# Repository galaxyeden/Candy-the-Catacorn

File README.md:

# Candy the Catacorn 🐱 + 🦄

[Update - I'm currently planning a board revision to make this easier to make with more obtainable parts]

Catacorn Badge :D I don't care how you spell it, I've spelled it catacorn for years. Caticorn is equally valid! It's really small, and cute - but you should be able to program it to do a lot of things.

You can [order from OSH Park](https://oshpark.com/shared_projects/pnVDiM8w) - that's not a sponsored link, and they're by no means the cheapest place to order from, I only link as they're probably the cheapest way to get a small number of purple boards with a lead-free finish (good as they'll be handled!) - and their service has always been good to me.

## Background

I have wanted to learn more about electrical engineering and the 'hardware' side of things, so have started playing with dev boards including the Adafruit Trinket M0, which is the board that inspired this project. But none of them were catacorn enough, so I decided to make one :)

It's also a great way to teach other people how to create microcontroller projects!

## Copyright/Liability

I'm not a lawyer, I believe everything I've based this on is licensed in a way I can draw inspiration, but let me know if you want me to get rid of something. All my work is Creative Commons, see license file. Also, I'm obviously not responsible for injuries or anything like that - this is definitely not a safety-tested, commercial project. Build at your own risk. It probably won't even work :)

## Basic Features

- ATSAMD21 microcontroller (ARM Cortext M0)
- Lots of LEDs, including two RGB ones (Dotstar-compatible)
- Two capacitive touch zones (ears)
- Native USB (you can even use it as a keyboard, hopefully)
- Probably a fair number of bugs and bad design decisions!

## Bill of Materials

| Component                               | Manufacturer                 | Qty |
|-----------------------------------------|------------------------------|-----|
| This board                              | Whoever you choose           | 1   |
| ATSAMD21E18A-AU-ND                      | Microchip Technology         | 1   |
| S2B-PH-SM4-TB(LF)(SN)                   | JST                          | 1   |
| 1uF 0603 Capacitor                      | Any                          | 2   |
| 10uF 0603 Capacitor                     | Any                          | 2   |
| APA102-5050 or Equivalent (e.g. SK9822) | APA Electronic Co (or other) | 2   |
| JE2835AWT-00-0000-000A0ZF940E           | Cree Inc                     | 2   |
| Pink LED 0805                           | Generic                      | 2   |
| Turquoise LED 0805                      | Generic                      | 3   |
| UV/Purple LED 0805                      | Generic                      | 3   |
| AP2112K-3.3TRG1                         | Diodes Incorporated          | 1   |
| DSS14UTR                                | SMC Diode Solutions          | 2   |
| USB3076-30-A                            | GCT                          | 1   |
| 150 Ohm 1206 Resistor                   | Any                          | 2   |
| 180 Ohm 0805 Resistor                   | Any                          | 2   |
| 180 Ohm 0603 Resistor                   | Any                          | 3   |
| 330 Ohm 0805 Resistor                   | Any                          | 3   |
| TL3342 Switch (or equivalent)           | E-Switch (or generic)        | 1   |

## How to use?

This board is intended to be used with either CircuitPython or [PlatformIO](https://platformio.org/). I have cloned and modified others [bootloader](https://github.com/MermaidAllie/uf2-samdx1/tree/master/build/alliecat_candythecatacorn) and [CircuitPython firmware](https://github.com/MermaidAllie/circuitpython/blob/5.0.x/ports/atmel-samd/build-alliecat_candythecatacorn/firmware.uf2). These are very similar to the Adafruit Trinket M0, just rebranded basically, and you can use Adafruit Trinket M0 bootloader/firmware with a lot of success (it's how I prototyped this).

I have also included PlatformIO code and board configuration.

## Thanks

Thank you to the following people:

- Ladyada and [Adafruit](https://learn.adafruit.com/how-to-program-samd-bootloaders/trinket-m0-wiring) - for building excellent products and teaching people electronics. I used a lot of Trinket M0's in prototyping this. Seriously, people, go buy their products - they're fantastic (and the boards are way cuter than some others, especially look at the Metro M4 Express - it's just adorable).

- Various inspirations for the catacorn, but especially to the kid who asked me to paint their face as a catacorn when I was face painting some years ago. It was the first time I really started thinking what the features of a catacorn should be like. I hope you're doing well today, and I wish you all the best in life :) - also to the many people who've drawn catacorns (and caticorns and unicats) online, and I've taken inspiration from.

- Also, on that note, credit to [Lisa Frank](https://lisafrank.com/) because cute Lisa Frank images were one of my childhood inspirations, and they're just awesome and made me like this style of art. A Google image search gave me more ideas for how to draw the board outline and even how to place components to be part of the art (e.g. using a capacitor as a nose, as one drawing I found had a very square nose). The purple Lisa Frank cat, especially, gave me the idea for how the whiskers could work on a component-kitty. And, only in Lisa Frank land do RGB LED cat eyes make sense :) 

- I found [this image from Freepik](https://www.freepik.com/free-vector/kawaii-style-unicorn-character-collection_4697393.htm#page=1&query=kawaii%20unicorn&position=7) which gave me inspiration for the general shape of the base (I needed something flatter than most to get the micro USB port in, and I liked how the cat's belly sat down) and head angle of the catacorn, and also for the style of the heart outline on the cheek. That said, Candy isn't a clone of anyone else's catacorn, with her tiny little horn and big glowing glittery heart, she has her own place in the world - and many others also provided inspiration. So credit to everyone who's drawn a catacorn that's in the first few pages of Google Images results :D

- [Emojipedia](https://emojipedia.org/) came in really useful to for bits of emoji-inspired inspiration, and the capacitive touch zones (which are the heart emoji from a font on my system).

- Q - for being an awesome friend who has helped with so much of the EDA side of working this all out. Thank you for answering late night messages with silly questions!

- Charlie - for coming up with the name Candy! I love you bestie :D Without your encouragement and inspiration, I wouldn't have achieved half the things I have with tech. Thank you <3

- JoJo Siwa - because the inspirational quote comes from one of your songs, and your concert on the [D.R.E.A.M. tour](https://www.jojodreamtour.com/) I went to in Cardiff was amazing. I'm not sure if it's your original quote tho, so I didn't quote it as you - I think I've heard it before? Either way, very inspiring performance! Keep things fun and positive and spread the positive energy, people!

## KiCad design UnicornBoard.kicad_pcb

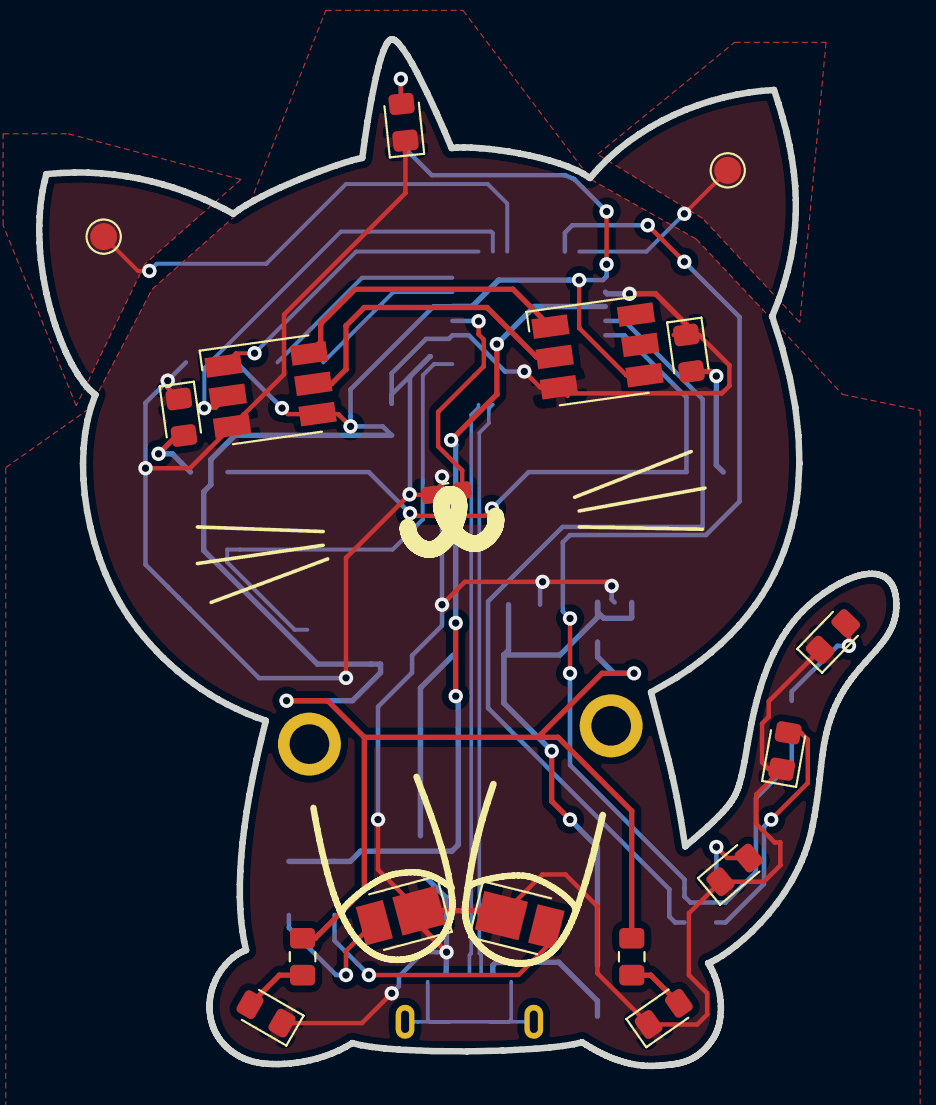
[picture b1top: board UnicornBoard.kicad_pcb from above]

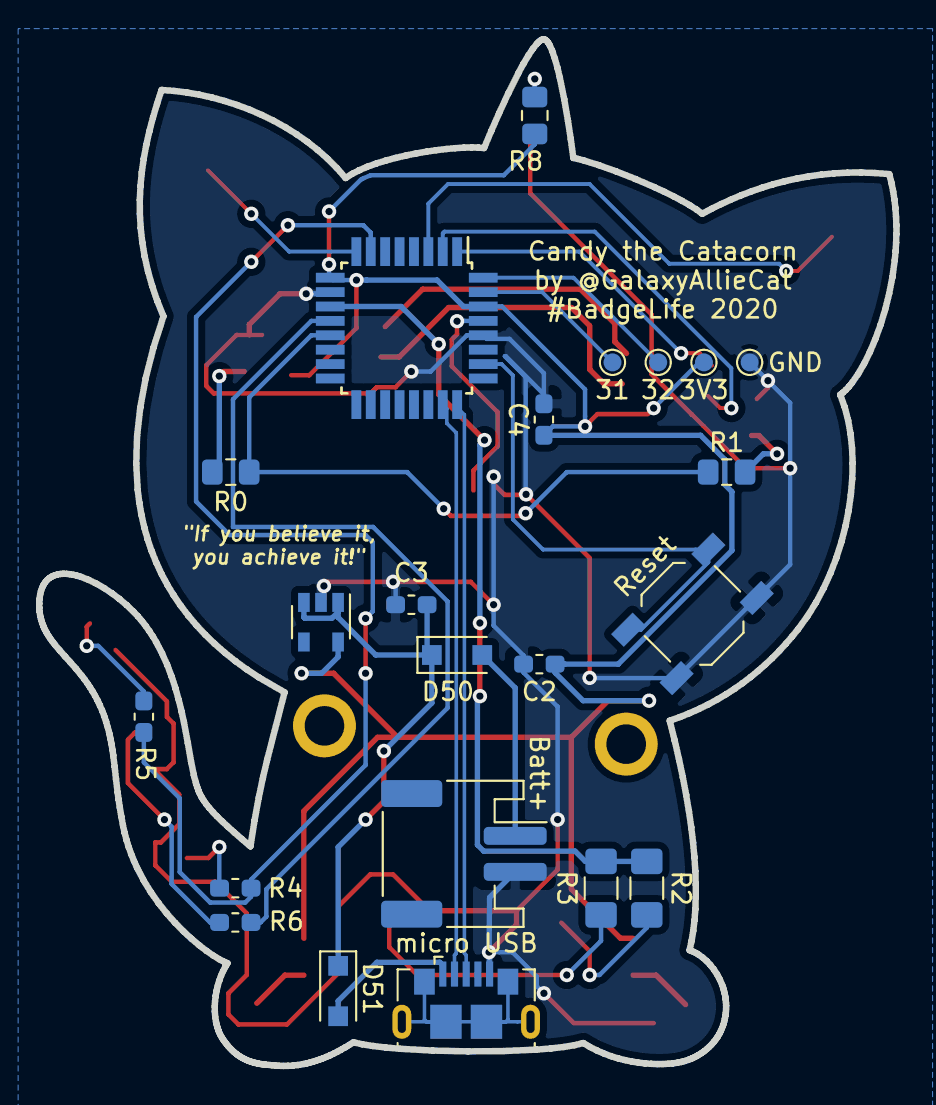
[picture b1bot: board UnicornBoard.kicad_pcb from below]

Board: 2 copper layers, 47.6 x 57.0 mm, 41 parts (22 on the bottom side), 31 nets.

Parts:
3V3, 31, 32: Conn_01x01; TestPoint_Pad_D1.0mm
Batt+: Battery; JST_PH_S2B-PH-SM4-TB_1x02-1MP_P2.00mm_Horizontal
C1, C4: 1 uF C; C_0603_1608Metric_Pad1.05x0.95mm_HandSolder
C2, C3: 10 uF C; C_0603_1608Metric_Pad1.05x0.95mm_HandSolder
D0, D1, D4, D5, D6, D7, D8, D9: LED; LED_0805_2012Metric_Pad1.15x1.40mm_HandSolder
D2, D3: LED; LED_PLCC_2835_Handsoldering
D50, D51: D_Schottky; D_SOD-123F
Dot1, Dot2: APA102; LED_RGB_5050-6
GND: Conn_01x01; TestPoint_Pad_D1.0mm
H1, H2: MountingHole; MountingHole_2.2mm_M2_ISO7380_Pad
R0, R1: 180R; R_0805_2012Metric_Pad1.15x1.40mm_HandSolder
R2, R3: 30R; R_1206_3216Metric_Pad1.42x1.75mm_HandSolder
R4, R5, R6: 100R; R_0603_1608Metric_Pad1.05x0.95mm_HandSolder
R7, R8, R9: 330R; R_0805_2012Metric_Pad1.15x1.40mm_HandSolder
Reset: SW_Push; SW_SPST_TL3342
Touch1, Touch2: MountingHole_Pad; TestPoint_Pad_D1.5mm
U1: ATSAMD21E18A-AU; TQFP-32_7x7mm_P0.8mm
U2: AP2112K-3.3; SOT-23-5
micro USB: USB_B_Micro; USB_Micro-B_GCT_USB3076-30-A

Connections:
+3V3: 3V3.1, C2.2, C4.1, Dot1.4, Dot2.4, R7.1, R8.1, R9.1, U1.9, U1.30, U2.5
+BATT: Batt+.1, D50.2
/USB_D+: U1.24, micro USB.3
/USB_D-: U1.23, micro USB.2
GND: Batt+.2, C1.1, C2.1, C3.2, C4.2, D0.1, D1.1, D2.1, D3.1, D4.1, D5.1, D6.1, D7.1, D8.1, D9.1, Dot1.3, Dot2.3, GND.1, Reset.2, U1.10, U1.28, U2.2, micro USB.5
unnamed: C1.2, U1.29
unnamed: C3.1, D50.1, D51.1, U2.1, U2.3
unnamed: D0.2, R0.2
unnamed: D1.2, R1.2
unnamed: D2.2, R2.1
unnamed: D3.2, R3.1
unnamed: D4.2, R4.2
unnamed: D5.2, R5.2
unnamed: D6.2, R6.2
unnamed: D7.2, R7.2
unnamed: D8.2, R8.2
unnamed: D9.2, R9.2
unnamed: Dot1.1, Dot2.6
unnamed: Dot1.2, Dot2.5
unnamed: Dot2.1, U1.1
unnamed: Dot2.2, U1.2
unnamed: 31.1, U1.31
unnamed: 32.1, U1.32
unnamed: R0.1, R1.1, U1.13
unnamed: R2.2, R3.2, U1.11
unnamed: R4.1, R5.1, U1.7
unnamed: R6.1, U1.12
unnamed: Reset.1, U1.26
unnamed: Touch1.1, U1.8
unnamed: Touch2.1, U1.3
VBUS: D51.2, micro USB.1

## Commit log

2020-01-17 First Version
2020-01-30 Candy the Catacorn
2020-01-31 Added BOM and tweaked resistor values to keep current in spec for GPIO pins
2020-01-31 Added inspirational quote to back silkscreen
2020-01-31 Updated readme with order link
2020-01-31 Added zipped gerbers to make easier to order
2020-02-03 Added Artwork
2020-02-11 Removed random no connect flags
2020-02-11 Fixed BOM
2020-02-12 Candy the Catacorn code
2020-02-13 Main.py initial release ready
2020-02-13 Light paws at start
2020-02-13 Made base state eyes pink/purple and less bright
2020-02-13 brighten paws slightly
2020-02-13 Added fade at end
2020-02-13 flipped paws
2020-02-16 Version 2, new outline
2020-02-16 Minor silk revision
2020-02-17 Candy Design
2020-05-01 Tiny change to clarify inspiration and learn Git
2020-05-04 Remove autosave files
2020-05-14 Updated GitHub username in main.py
2020-05-24 Re-organise and setup for move to PlatformIO
2020-05-24 eased disclaimed
2020-05-24 More layout to PlatformIO config
2020-05-24 Added CONTRIBUTING
2020-05-24 added example py
2020-05-24 Removed zephyr framework option
2020-05-24 Minimal Working C++
2020-05-25 custom variant with working PWM eyes
2020-05-25 Initial GitHub Pages Layout
2020-05-25 New revision Osh Park link
2020-05-25 Fixed broken image
2020-05-25 cropped profile pic
2020-05-25 more pages info
2020-05-25 Added setup code for cap touch
2020-05-25 test code, no cap touch
2020-05-25 updated home
2020-05-25 first working cap touch
2020-05-25 Corrected colour order, added mode
2020-05-25 added turquoise mode
2020-05-25 sep left ear
2020-05-25 fixed <>
2020-05-25 added right ear rainbow
2020-05-25 added comments
2020-05-25 Improved rainbow, fixed blackout
2020-05-31 description shortened
2020-05-31 Emojification and firmware diffs
2020-05-31 bold to italic
2020-05-31 improved readability
2020-06-03 GitHub Pages Branch renaming prep
2020-06-03 Set theme jekyll-theme-minimal
2020-06-05 typo fixed
2020-06-25 noted pin functions
2020-06-25 fixed url
2020-12-29 Moved light show to function
2020-12-29 Moved rainbow generator to function
2020-12-29 Added some comments - more will come
2020-12-29 Updated URL to HTTPS
2021-01-05 hello
2021-01-06 test
2021-01-07 Testing Jupyter
2021-01-07 Jupyter test 2
2021-01-08 Jupyter test 3
2021-01-08 Remove Jupyter test
2021-03-05 Updated to en-US
2021-07-31 Proposed changes
    Hey Allie, I think we should include this!
2022-01-15 US spelling of colors
2022-01-20 remove unused directories
2022-06-16 start of dev for v2
2022-06-16 Add VREG symbol
2022-06-16 thurs evening
